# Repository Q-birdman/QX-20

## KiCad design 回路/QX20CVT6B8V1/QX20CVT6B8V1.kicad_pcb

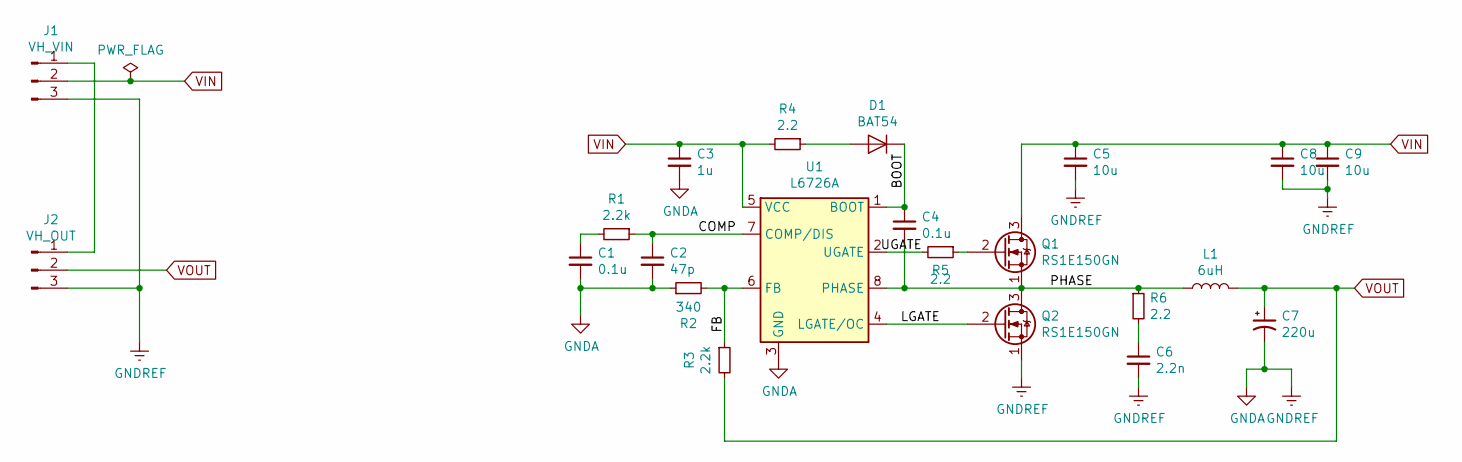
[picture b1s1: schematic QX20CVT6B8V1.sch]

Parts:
C1, C4: 0.1u; C_1206_3216Metric_Pad1.42x1.75mm_HandSolder
C2: 47p; C_1206_3216Metric_Pad1.42x1.75mm_HandSolder
C3: 1u; C_1206_3216Metric_Pad1.42x1.75mm_HandSolder
C5, C8, C9: 10u; C_1206_3216Metric_Pad1.42x1.75mm_HandSolder
C6: 2.2n; C_1206_3216Metric_Pad1.42x1.75mm_HandSolder
C7: 220u; CP_Radial_D8.0mm_P3.50mm
D1: BAT54; D_SOD-323_HandSoldering
J1: VH_VIN; JST_VH_B3PS-VH_1x03_P3.96mm_Horizontal
J2: VH_OUT; JST_VH_B3P-VH-B_1x03_P3.96mm_Vertical
L1: 6uH; L_Bourns_SRP1250
Q1, Q2: RS1E150GN; VSONP-8-1EP_5x6_P1.27mm
R1, R3: 2.2k; R_1206_3216Metric_Pad1.42x1.75mm_HandSolder
R2: 340; R_1206_3216Metric_Pad1.42x1.75mm_HandSolder
R4, R5, R6: 2.2; R_1206_3216Metric_Pad1.42x1.75mm_HandSolder
U1: L6726A; SOIC-8_3.9x4.9mm_P1.27mm

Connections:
/BOOT: C4.1, D1.1 (K), U1.1 (BOOT)
/COMP: C2.1, R1.1, U1.7 (COMP/DIS)
/FB: R2.2, R3.1, U1.6 (FB)
/LGATE: Q2.2 (G), U1.4 (LGATE/OC)
/PHASE: C4.2, L1.1, Q1.1 (S), Q2.3 (D), R6.1, U1.8 (PHASE)
/UGATE: R5.2, U1.2 (UGATE)
GNDA: C1.2, C2.2, C3.2, C5.2, C6.2, C7.2, C8.2, C9.2, J1.3, J2.3, Q2.1 (S), R2.1, U1.3 (GND)
unnamed: C1.1, R1.2
unnamed: C6.1, R6.2
unnamed: D1.2 (A), R4.1
unnamed: J1.1, J2.1
unnamed: Q1.2 (G), R5.1
VIN: C3.1, C5.1, C8.1, C9.1, J1.2, Q1.3 (D), R4.2, U1.5 (VCC)
VOUT: C7.1, J2.2, L1.2, R3.2

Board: 2 copper layers, 22 parts (0 on the bottom side), 14 nets, no tracks yet.

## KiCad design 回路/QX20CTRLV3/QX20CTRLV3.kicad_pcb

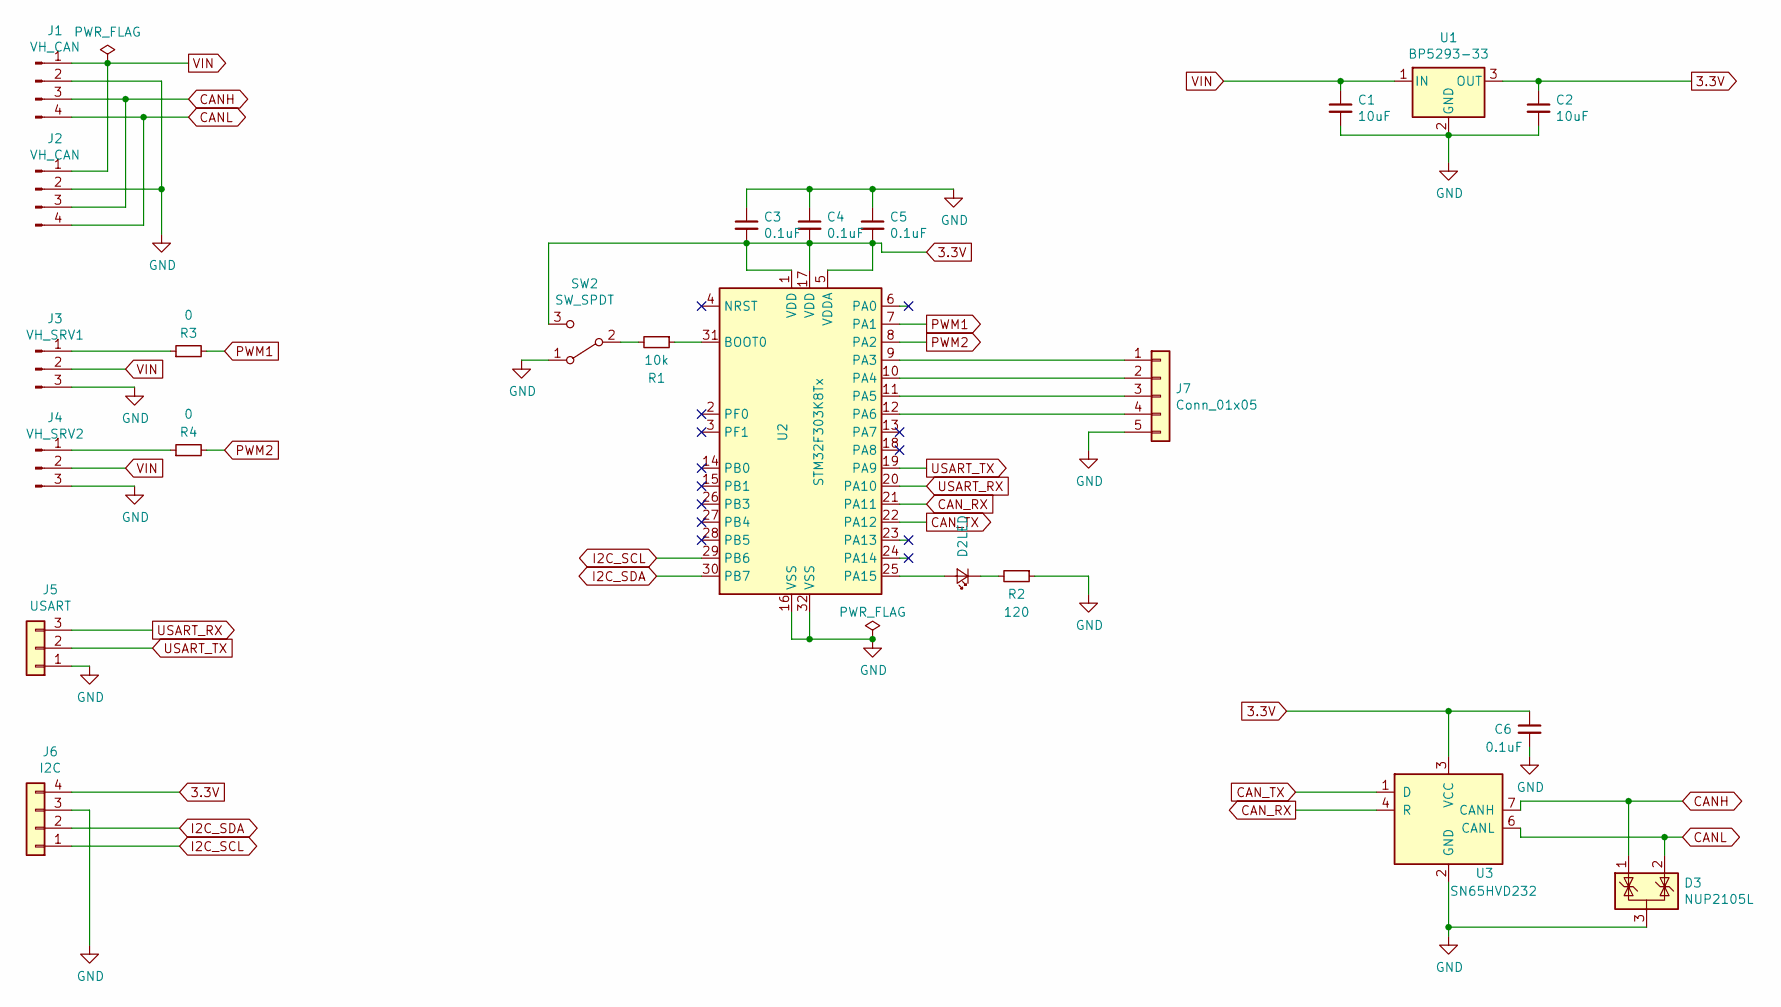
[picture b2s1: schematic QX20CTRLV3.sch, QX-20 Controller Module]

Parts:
C1, C2: 10uF; C_1206_3216Metric_Pad1.42x1.75mm_HandSolder
C3, C4, C5, C6: 0.1uF; C_1206_3216Metric_Pad1.42x1.75mm_HandSolder
D2: LED; D_1206_3216Metric_Pad1.42x1.75mm_HandSolder
D3: NUP2105L; SOT-23
J1, J2: VH_CAN; JST_VH_B4PS-VH_1x04_P3.96mm_Horizontal
J3: VH_SRV1; JST_VH_B3PS-VH_1x03_P3.96mm_Horizontal
J4: VH_SRV2; JST_VH_B3PS-VH_1x03_P3.96mm_Horizontal
J5: USART; JST_XH_B3B-XH-A_1x03_P2.50mm_Vertical
J6: I2C; JST_XH_B4B-XH-A_1x04_P2.50mm_Vertical
J7: Conn_01x05; JST_XH_B5B-XH-A_1x05_P2.50mm_Vertical
R1: 10k; R_1206_3216Metric_Pad1.42x1.75mm_HandSolder
R2: 120; R_1206_3216Metric_Pad1.42x1.75mm_HandSolder
R3, R4: 0; R_1206_3216Metric_Pad1.42x1.75mm_HandSolder
SW2: SW_SPDT; PinHeader_1x03_P2.54mm_Vertical
U1: BP5293-33; TO-220-3_Vertical
U2: STM32F303K8Tx; LQFP-32_7x7mm_P0.8mm
U3: SN65HVD232; SOIC-8_3.9x4.9mm_P1.27mm

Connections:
3.3V: C2.1, C3.2, C4.2, C5.2, C6.1, J6.4, SW2.3 (C), U1.3 (OUT), U2.1 (VDD), U2.5 (VDDA), U2.17 (VDD), U3.3 (VCC)
CANH: D3.1 (K), J1.3, J2.3, U3.7 (CANH)
CANL: D3.2 (K), J1.4, J2.4, U3.6 (CANL)
CAN_RX: U2.21 (PA11), U3.4 (R)
CAN_TX: U2.22 (PA12), U3.1 (D)
GND: C1.2, C2.2, C3.1, C4.1, C5.1, C6.2, D3.3 (A), J1.2, J2.2, J3.3, J4.3, J5.1, J6.3, J7.5, R2.1, SW2.1 (A), U1.2 (GND), U2.16 (VSS), U2.32 (VSS), U3.2 (GND)
I2C_SCL: J6.1, U2.29 (PB6)
I2C_SDA: J6.2, U2.30 (PB7)
unnamed: D2.1 (K), R2.2
unnamed: D2.2 (A), U2.25 (PA15)
unnamed: J3.1, R3.1
unnamed: J4.1, R4.1
unnamed: J7.1, U2.9 (PA3)
unnamed: J7.2, U2.10 (PA4)
unnamed: J7.3, U2.11 (PA5)
unnamed: J7.4, U2.12 (PA6)
unnamed: R1.1, U2.31 (BOOT0)
unnamed: R1.2, SW2.2 (B)
PWM1: R3.2, U2.7 (PA1)
PWM2: R4.2, U2.8 (PA2)
USART_RX: J5.3, U2.20 (PA10)
USART_TX: J5.2, U2.19 (PA9)
VIN: C1.1, J1.1, J2.1, J3.2, J4.2, U1.1 (IN)

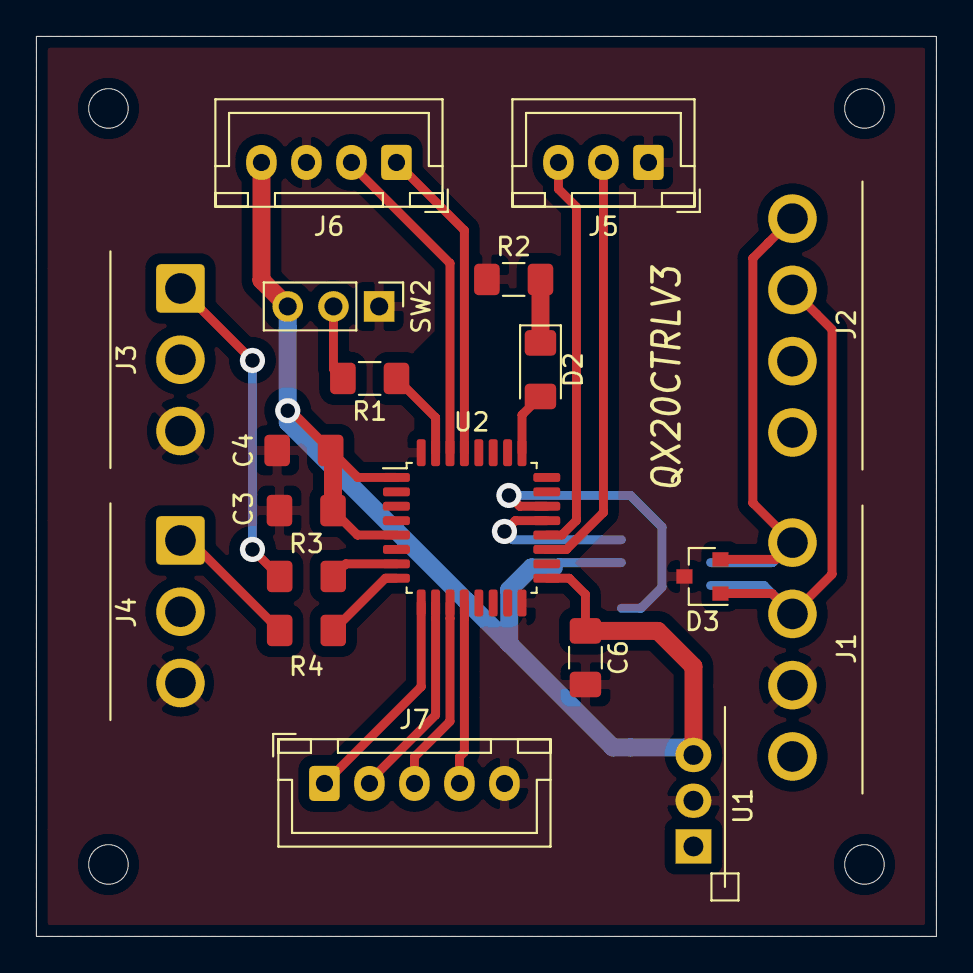
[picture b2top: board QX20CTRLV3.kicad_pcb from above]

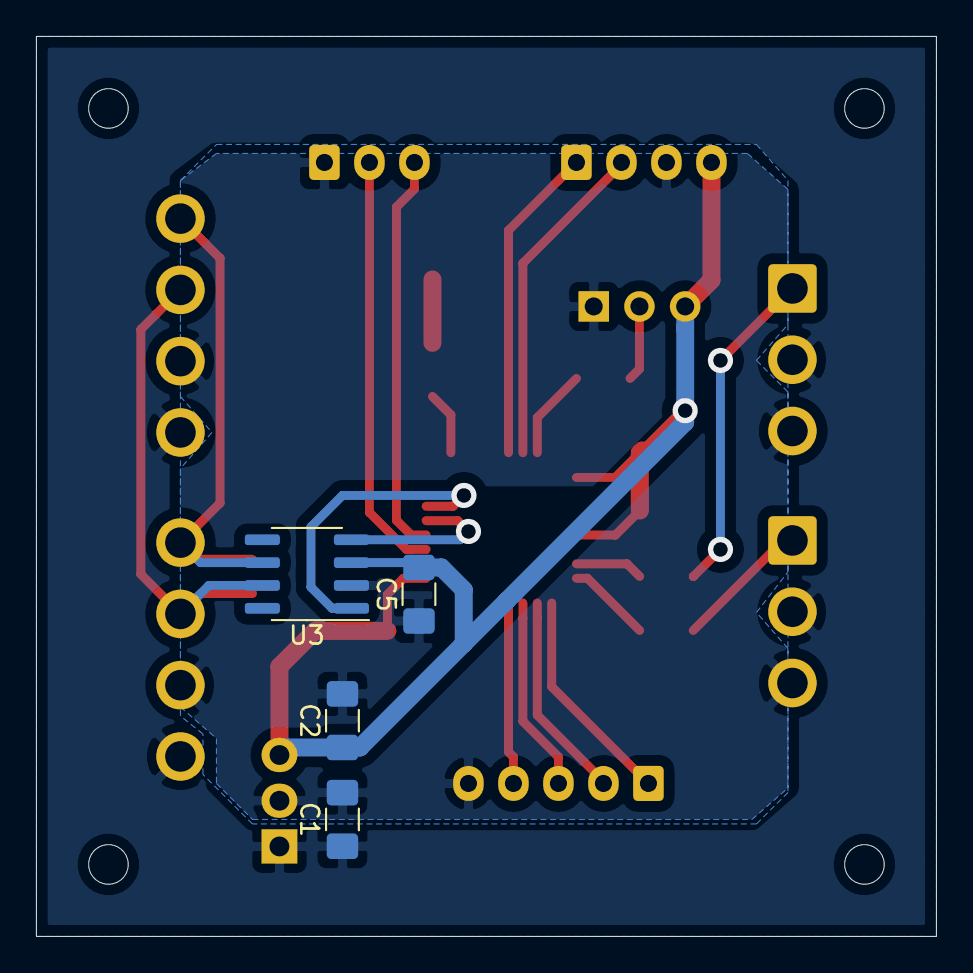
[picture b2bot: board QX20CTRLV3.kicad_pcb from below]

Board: 2 copper layers, 50.0 x 50.0 mm, 23 parts (4 on the bottom side), 23 nets.

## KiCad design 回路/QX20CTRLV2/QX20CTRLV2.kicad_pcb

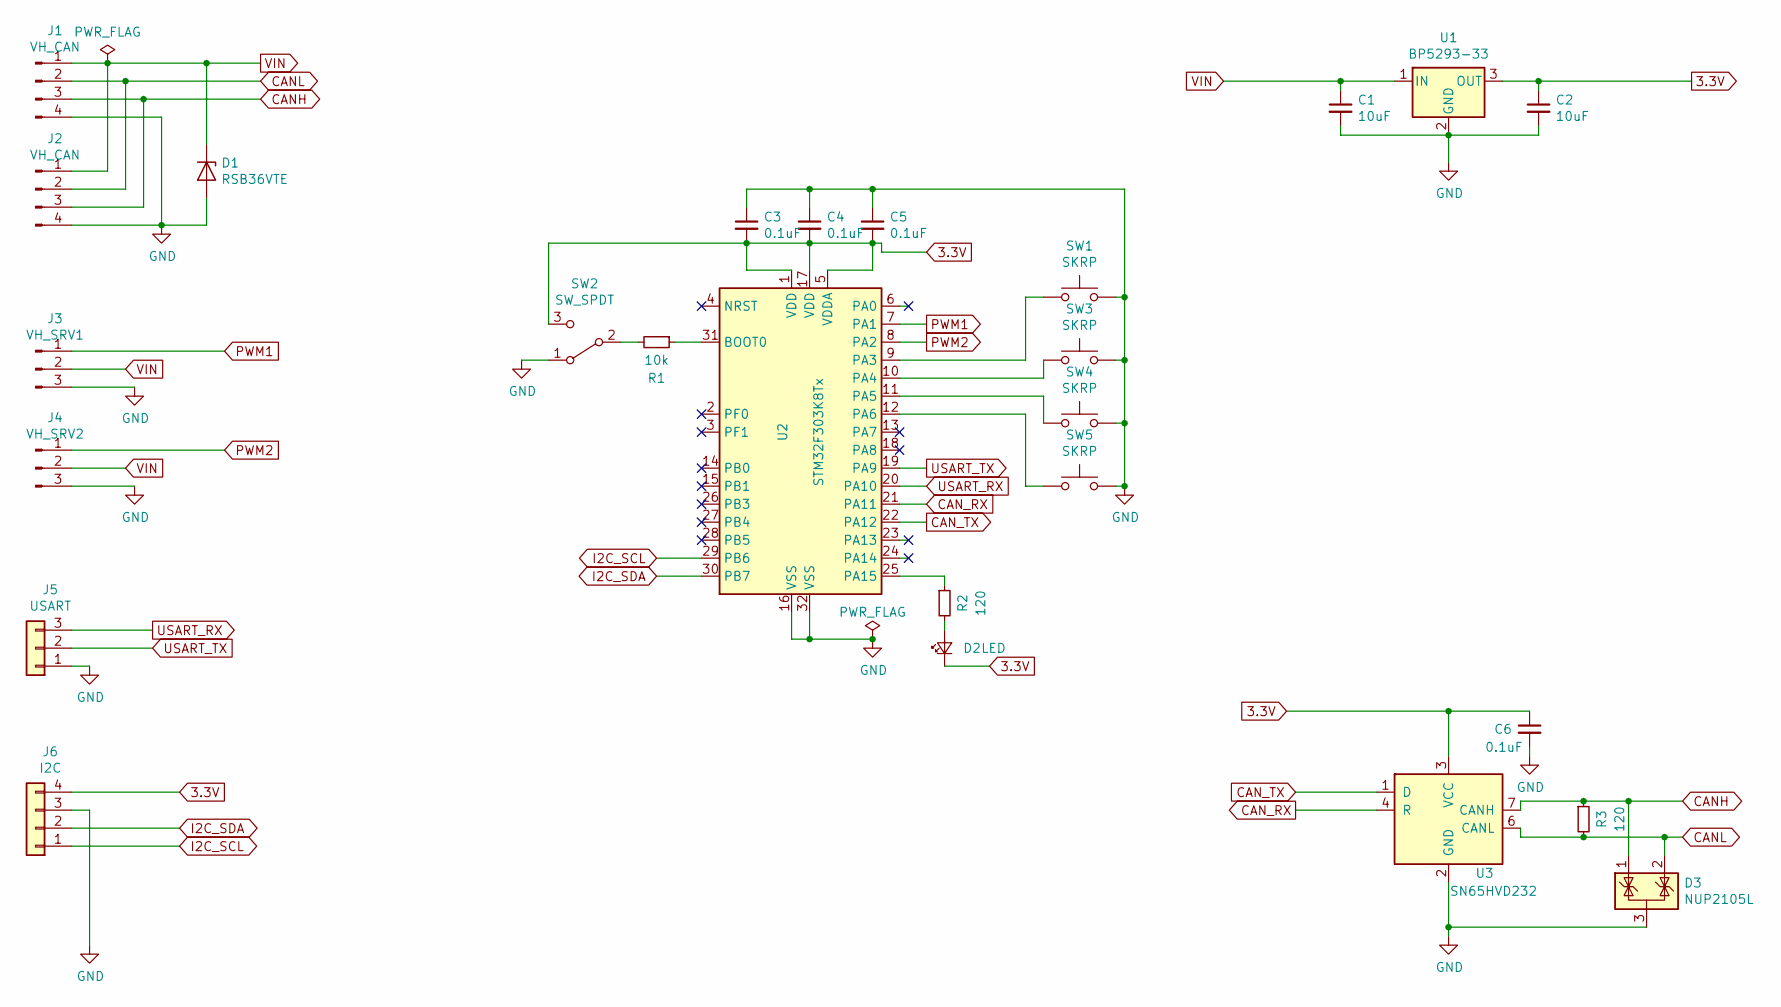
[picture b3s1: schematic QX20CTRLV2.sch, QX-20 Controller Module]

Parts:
C1, C2: 10uF; C_1206_3216Metric_Pad1.42x1.75mm_HandSolder
C3, C4, C5, C6: 0.1uF; C_1206_3216Metric_Pad1.42x1.75mm_HandSolder
D1: RSB36VTE; D_SOD-323_HandSoldering
D2: LED; D_1206_3216Metric_Pad1.42x1.75mm_HandSolder
D3: NUP2105L; SOT-23
J1, J2: VH_CAN; JST_VH_B4PS-VH_1x04_P3.96mm_Horizontal
J3: VH_SRV1; JST_VH_B3PS-VH_1x03_P3.96mm_Horizontal
J4: VH_SRV2; JST_VH_B3PS-VH_1x03_P3.96mm_Horizontal
J5: USART; PinSocket_1x03_P2.54mm_Vertical
J6: I2C; PinSocket_1x04_P2.54mm_Vertical
R1: 10k; R_1206_3216Metric_Pad1.42x1.75mm_HandSolder
R2, R3: 120; R_1206_3216Metric_Pad1.42x1.75mm_HandSolder
SW1, SW3, SW4, SW5: SKRP; SW_SPST_PTS810
SW2: SW_SPDT; PinHeader_1x03_P2.54mm_Vertical
U1: BP5293-33; TO-220-3_Vertical
U2: STM32F303K8Tx; LQFP-32_7x7mm_P0.8mm
U3: SN65HVD232; SOIC-8_3.9x4.9mm_P1.27mm

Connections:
3.3V: C2.1, C3.2, C4.2, C5.2, C6.1, D2.1 (K), J6.4, SW2.3 (C), U1.3 (OUT), U2.1 (VDD), U2.5 (VDDA), U2.17 (VDD), U3.3 (VCC)
CANH: D3.1 (K), J1.3, J2.3, R3.1, U3.7 (CANH)
CANL: D3.2 (K), J1.2, J2.2, R3.2, U3.6 (CANL)
CAN_RX: U2.21 (PA11), U3.4 (R)
CAN_TX: U2.22 (PA12), U3.1 (D)
GND: C1.2, C2.2, C3.1, C4.1, C5.1, C6.2, D1.2 (A), D3.3 (A), J1.4, J2.4, J3.3, J4.3, J5.1, J6.3, SW1.2, SW2.1 (A), SW3.2, SW4.2, SW5.2, U1.2 (GND), U2.16 (VSS), U2.32 (VSS), U3.2 (GND)
I2C_SCL: J6.1, U2.29 (PB6)
I2C_SDA: J6.2, U2.30 (PB7)
unnamed: D2.2 (A), R2.2
unnamed: R1.1, U2.31 (BOOT0)
unnamed: R1.2, SW2.2 (B)
unnamed: R2.1, U2.25 (PA15)
unnamed: SW1.1, U2.9 (PA3)
unnamed: SW3.1, U2.10 (PA4)
unnamed: SW4.1, U2.11 (PA5)
unnamed: SW5.1, U2.12 (PA6)
PWM1: J3.1, U2.7 (PA1)
PWM2: J4.1, U2.8 (PA2)
USART_RX: J5.3, U2.20 (PA10)
USART_TX: J5.2, U2.19 (PA9)
VIN: C1.1, D1.1 (K), J1.1, J2.1, J3.2, J4.2, U1.1 (IN)

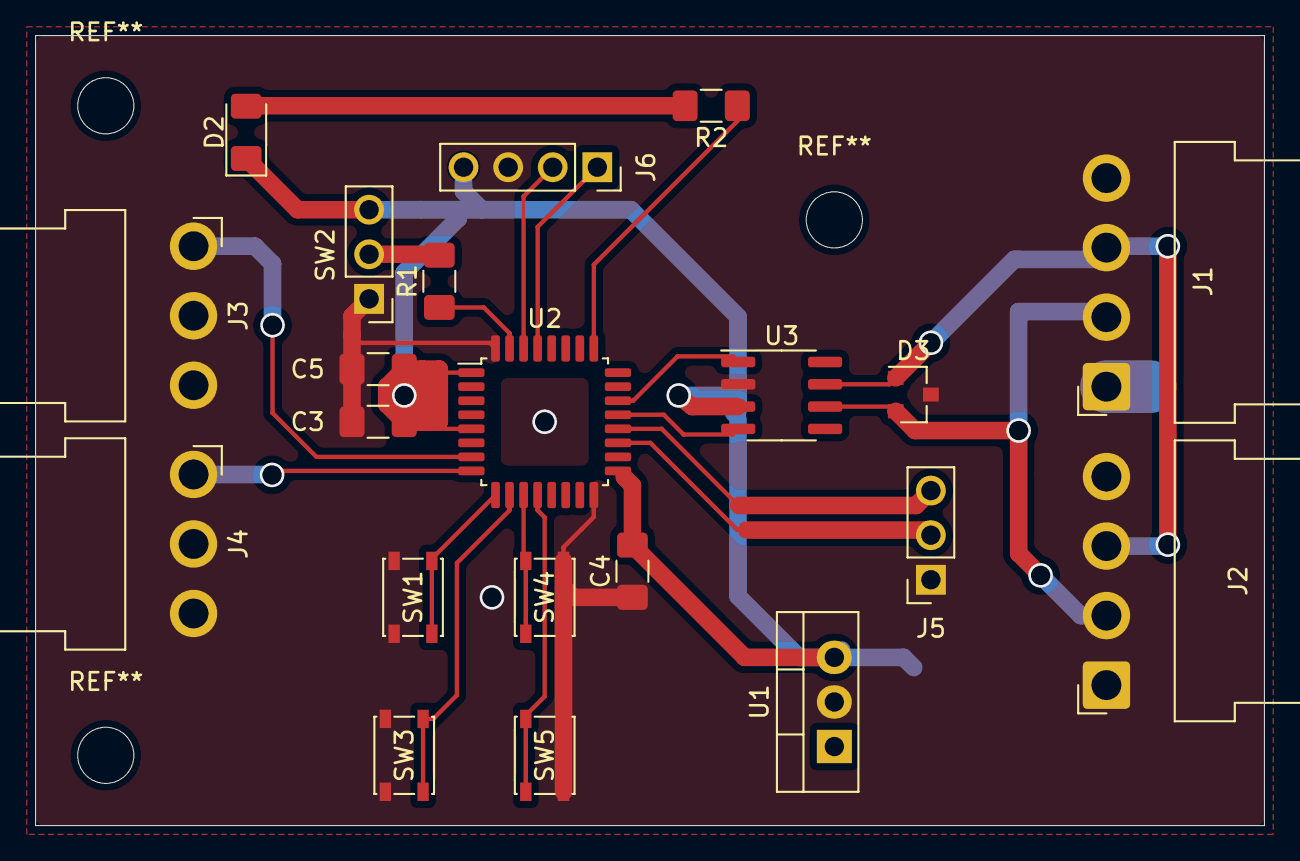
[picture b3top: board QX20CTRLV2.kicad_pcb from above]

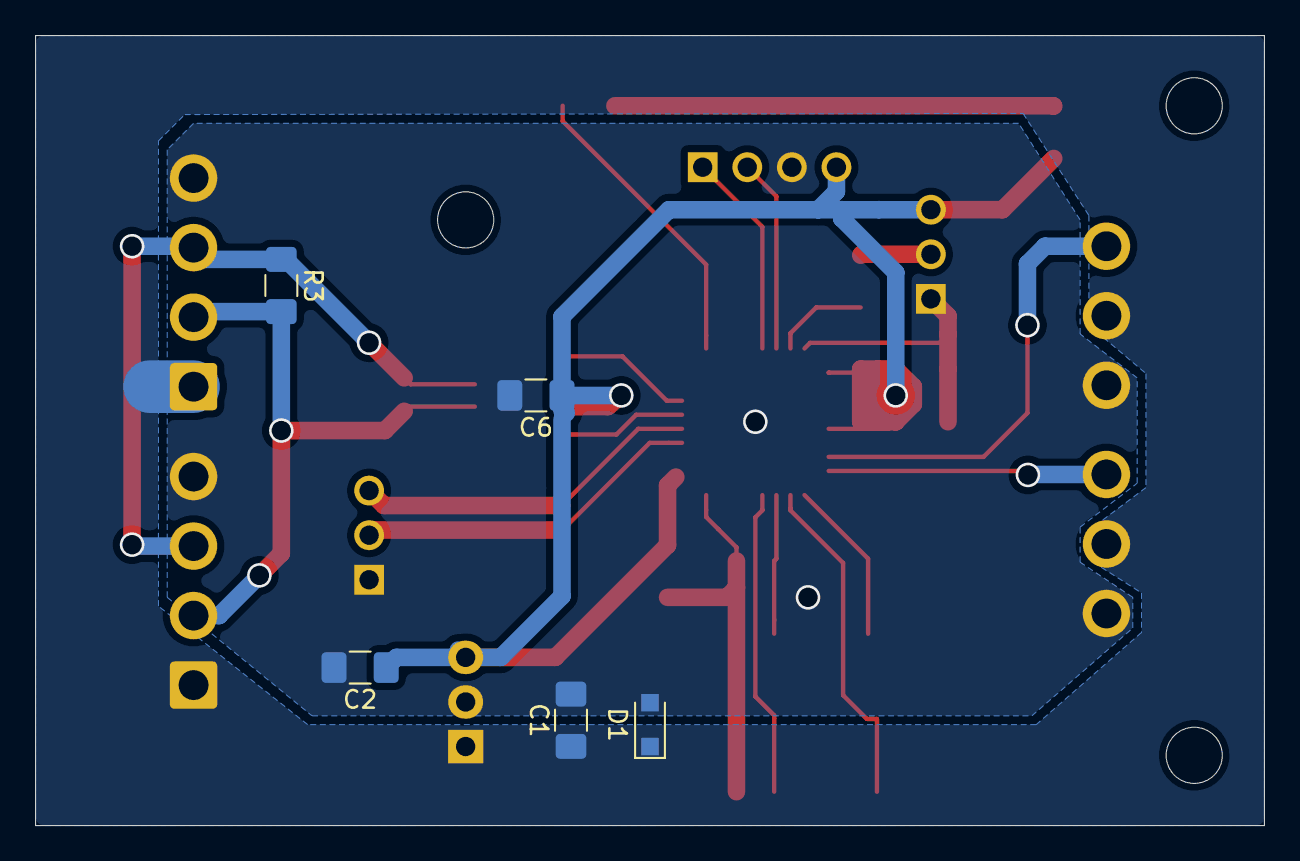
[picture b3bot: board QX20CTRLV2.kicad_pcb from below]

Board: 2 copper layers, 70.0 x 45.0 mm, 26 parts (5 on the bottom side), 21 nets.

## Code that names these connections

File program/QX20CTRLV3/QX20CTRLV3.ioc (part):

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Mcu.Name=STM32F303K(6-8)Tx
Mcu.Package=LQFP32
Mcu.UserName=STM32F303K8Tx
PA1.Signal=S_TIM2_CH2
PA10.Mode=Asynchronous
PA10.Signal=USART1_RX
PA11.Mode=Master
PA11.Signal=CAN_RX
PA12.Mode=Master
PA12.Signal=CAN_TX
PA15.Signal=GPIO_Output
PA2.Signal=S_TIM2_CH3
PA3.GPIOParameters=GPIO_PuPd,GPIO_ModeDefaultEXTI
PA3.GPIO_ModeDefaultEXTI=GPIO_MODE_IT_RISING_FALLING
PA3.GPIO_PuPd=GPIO_PULLUP
PA3.Signal=GPXTI3
PA4.GPIOParameters=GPIO_PuPd,GPIO_ModeDefaultEXTI
PA4.GPIO_ModeDefaultEXTI=GPIO_MODE_IT_RISING_FALLING
PA4.GPIO_PuPd=GPIO_PULLUP
PA4.Signal=GPXTI4
PA5.GPIOParameters=GPIO_PuPd,GPIO_ModeDefaultEXTI
PA5.GPIO_ModeDefaultEXTI=GPIO_MODE_IT_RISING_FALLING
PA5.GPIO_PuPd=GPIO_PULLUP
PA5.Signal=GPXTI5
PA6.GPIOParameters=GPIO_PuPd,GPIO_ModeDefaultEXTI
PA6.GPIO_ModeDefaultEXTI=GPIO_MODE_IT_RISING_FALLING
PA6.GPIO_PuPd=GPIO_PULLUP
PA6.Signal=GPXTI6
PA9.Mode=Asynchronous
PA9.Signal=USART1_TX
RCC.HSEPLLFreq_Value=8000000
RCC.HSE_VALUE=8000000
RCC.SYSCLKFreq_VALUE=36000000
RCC.SYSCLKSourceVirtual=RCC_SYSCLKSOURCE_PLLCLK
board=custom

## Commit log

2019-09-11 空のデータ送っちゃった!
2019-09-11 私がQiitaに上げてる講座のプログラムです。気になる方はご確認ください。 また、テストで上げたファイルは削除しました。
2019-09-11 距離センサーと七セグ
    作りました
2019-10-04 gitignore編集
    藤田が試しにやりました。
2019-10-30 電装講座No.4を追加しました。
2019-10-30 imamuraww
2019-10-30 wejanakuteme
2019-10-30 no.4のメインプログラムです。
2019-11-01 小さめの修正
2019-11-08 可変抵抗器で出力できるようにしたつもり。
2019-11-08 ちゃんと出るように改善しました。
2019-11-08 光度が数値で出るように
2019-11-09 今できてるもの
2019-11-11 フォルダ整理
    「プログラム」等日本語だとバグるので、名前変更。
2019-11-14 QX20CTRLPOCV0
    QX20 CTRL POC用
    角度出し時使用プログラム
    VSCode上環境での使用前提
2019-11-20 ﾊﾝﾁｮｳのおもちゃ。
2019-11-28 飛行試験時プログラム
2019-12-12 pyデータの作成/video対応
2019-12-22 きちんと動くようにしました。
2019-12-23 QX20CTRLV1 回路図
    QX20 コントローラー
    + STM32F303K8T6
    + サーボ 2ch
    + I2C, USART, SWD(debug)
    + LED*1
    + 活線挿抜対応
2019-12-26 for jetson
2019-12-26 jetson用
2019-12-28 名前変更、待機時間
2020-02-18 QX20CTRLV2
    QX20コントローラーV2 NC基板用
    回路図、実装図、ガーバーデータまで。
2020-02-28 QX20CTRLV2 ガーバーデータ
2020-03-11 QX20CTRLV3
2020-03-15 QX20CTRLV3発注仕様
2020-03-26 changed for mac 3/25
2020-04-03 QX20CBT6B8V1 回路図
2020-10-21 QX20CTRLV3
    たまっていた分を更新...
2020-11-02 QX20CTRLV3 サーボ回転のバグ修正
2020-11-18 QX20CTRLV3 途中
2020-12-11 QX20CTRLV3 途中
    やらんとあかんよ
